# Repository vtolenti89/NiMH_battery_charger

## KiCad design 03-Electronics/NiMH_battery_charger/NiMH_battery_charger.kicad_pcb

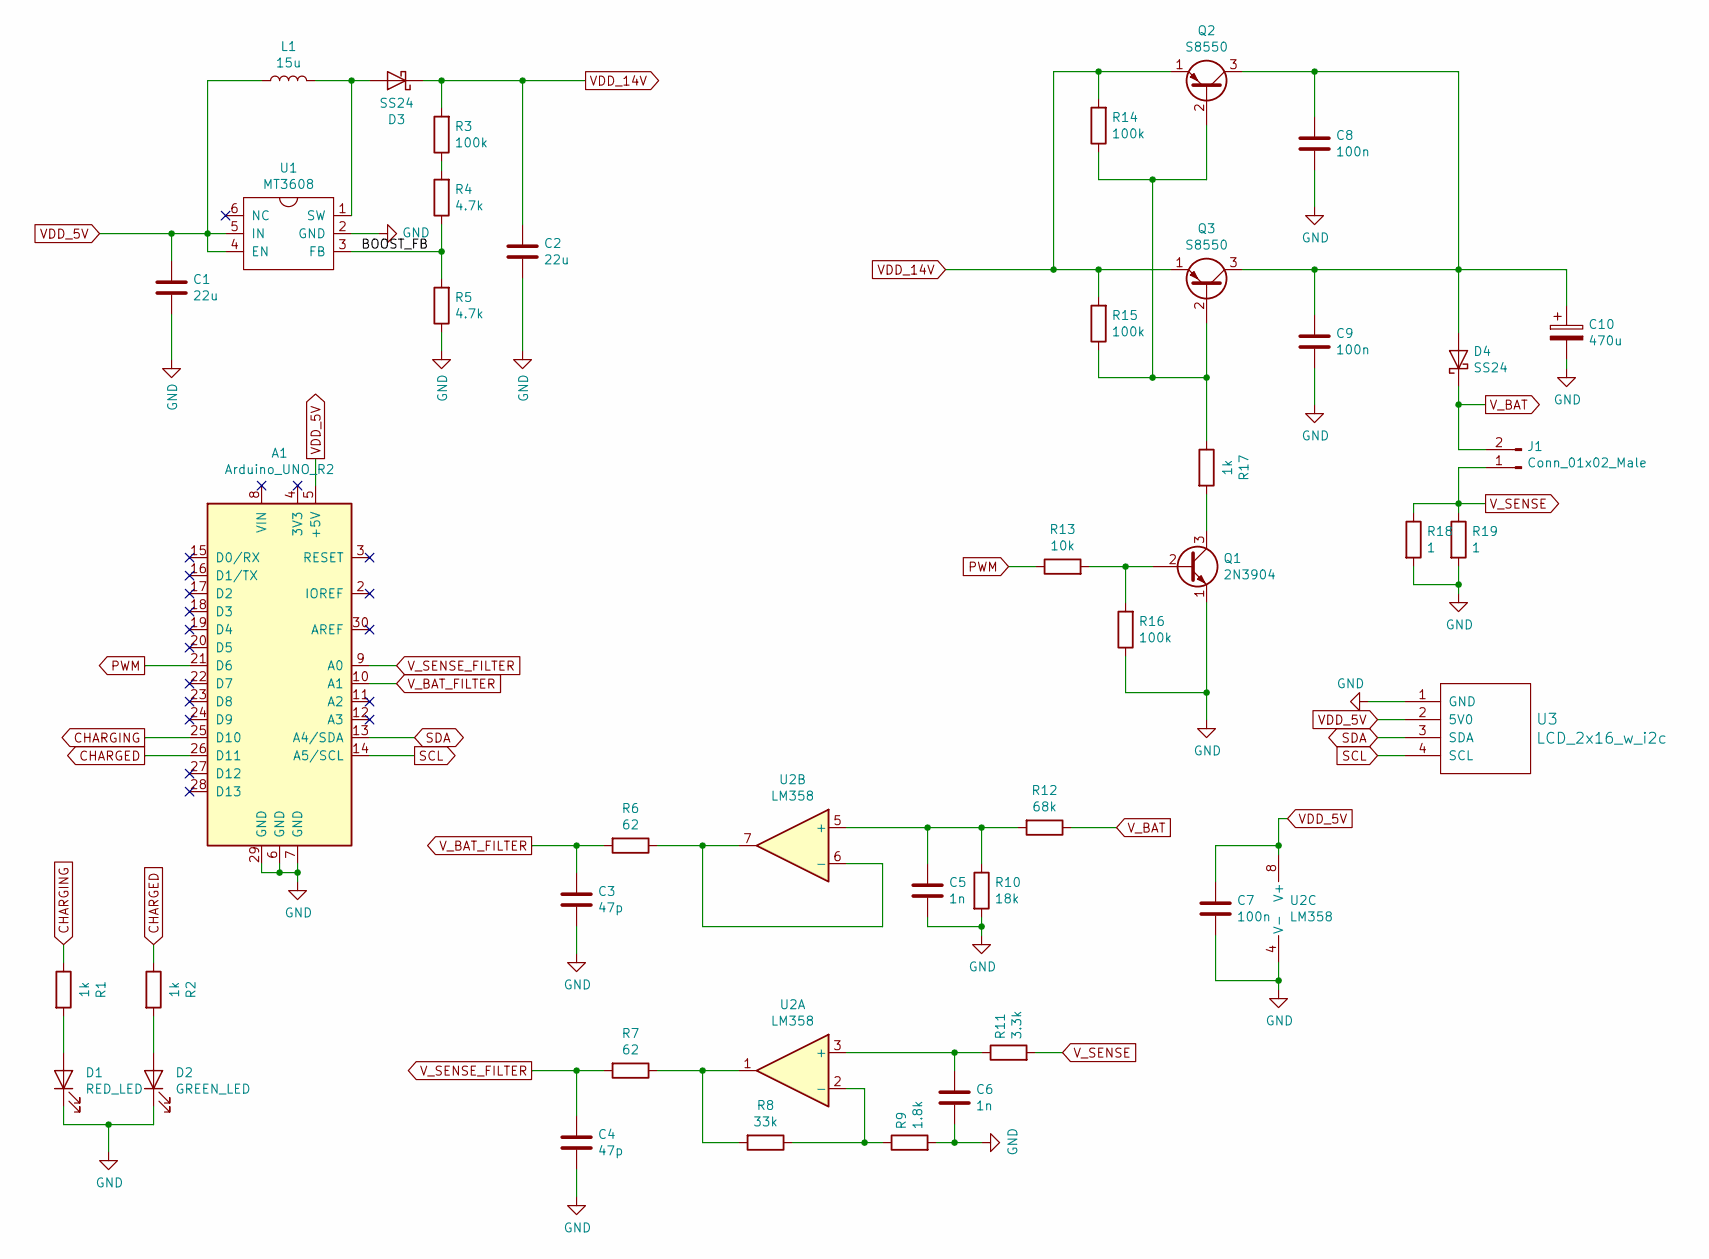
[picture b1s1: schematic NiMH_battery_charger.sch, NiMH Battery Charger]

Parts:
A1: Arduino_UNO_R2
C1, C2: 22u; C_0603_1608Metric_Pad1.05x0.95mm_HandSolder
C3, C4: 47p; C_0603_1608Metric_Pad1.05x0.95mm_HandSolder
C5, C6: 1n; C_0603_1608Metric_Pad1.05x0.95mm_HandSolder
C7, C8, C9: 100n; C_0603_1608Metric_Pad1.05x0.95mm_HandSolder
C10: 470u; CP_Radial_D6.3mm_P2.50mm
D1: RED_LED; LED_1206_3216Metric
D2: GREEN_LED; LED_1206_3216Metric
D3, D4: SS24; SMA_DO-214AC
J1: Conn_01x02_Male; PinSocket_1x02_P2.54mm_Vertical
L1: 15u; CD54
Q1: 2N3904; TO-92_Inline
Q2, Q3: S8550; TO-92_Inline
R1, R2, R17: 1k; R_0603_1608Metric_Pad1.05x0.95mm_HandSolder
R3, R14, R15, R16: 100k; R_0603_1608Metric_Pad1.05x0.95mm_HandSolder
R4, R5: 4.7k; R_0603_1608Metric_Pad1.05x0.95mm_HandSolder
R6, R7: 62; R_0603_1608Metric_Pad1.05x0.95mm_HandSolder
R8: 33k; R_0603_1608Metric_Pad1.05x0.95mm_HandSolder
R9: 1.8k; R_0603_1608Metric_Pad1.05x0.95mm_HandSolder
R10: 18k; R_0603_1608Metric_Pad1.05x0.95mm_HandSolder
R11: 3.3k; R_0603_1608Metric_Pad1.05x0.95mm_HandSolder
R12: 68k; R_0603_1608Metric_Pad1.05x0.95mm_HandSolder
R13: 10k; R_0603_1608Metric_Pad1.05x0.95mm_HandSolder
R18, R19: 1; R_0603_1608Metric_Pad1.05x0.95mm_HandSolder
U1: MT3608; TSOT-23-6
U2: LM358; SOIC-8-1EP_3.9x4.9mm_P1.27mm_EP2.29x3mm
U3: LCD_2x16_w_i2c; PinHeader_1x04_P2.54mm_Vertical

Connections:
/BOOST_FB: R4.1, R5.2, U1.3 (FB)
CHARGED: A1.26 (D11), R2.1
CHARGING: A1.25 (D10), R1.1
GND: A1.6 (GND), A1.7 (GND), A1.29 (GND), C1.2, C2.2, C3.2, C4.2, C5.2, C6.2, C7.2, C8.2, C9.2, C10.2, D1.1 (K), D2.1 (K), Q1.1 (E), R5.1, R9.2, R10.2, R16.1, R18.2, R19.2, U1.2 (GND), U2.4 (V-), U3.1 (GND)
unnamed: C5.1, R10.1, R12.2, U2.5 (+)
unnamed: C6.1, R11.1, U2.3 (+)
unnamed: C8.1, C9.1, C10.1, D4.2 (A), Q2.3 (C), Q3.3 (C)
unnamed: D1.2 (A), R1.2
unnamed: D2.2 (A), R2.2
unnamed: D3.2 (A), L1.2, U1.1 (SW)
unnamed: Q1.2 (B), R13.2, R16.2
unnamed: Q1.3 (C), R17.2
unnamed: Q2.2 (B), Q3.2 (B), R14.1, R15.1, R17.1
unnamed: R3.1, R4.2
unnamed: R6.1, U2.6 (-), U2.7
unnamed: R7.1, R8.2, U2.1
unnamed: R8.1, R9.1, U2.2 (-)
PWM: A1.21 (D6), R13.1
SCL: A1.14 (A5/SCL), U3.4 (SCL)
SDA: A1.13 (A4/SDA), U3.3 (SDA)
VDD_5V: A1.5 (+5V), C1.1, C7.1, L1.1, U1.4 (EN), U1.5 (IN), U2.8 (V+), U3.2 (5V0)
VDD_14V: C2.1, D3.1 (K), Q2.1 (E), Q3.1 (E), R3.2, R14.2, R15.2
V_BAT: D4.1 (K), J1.2, R12.1
V_BAT_FILTER: A1.10 (A1), C3.1, R6.2
V_SENSE: J1.1, R11.2, R18.1, R19.1
V_SENSE_FILTER: A1.9 (A0), C4.1, R7.2

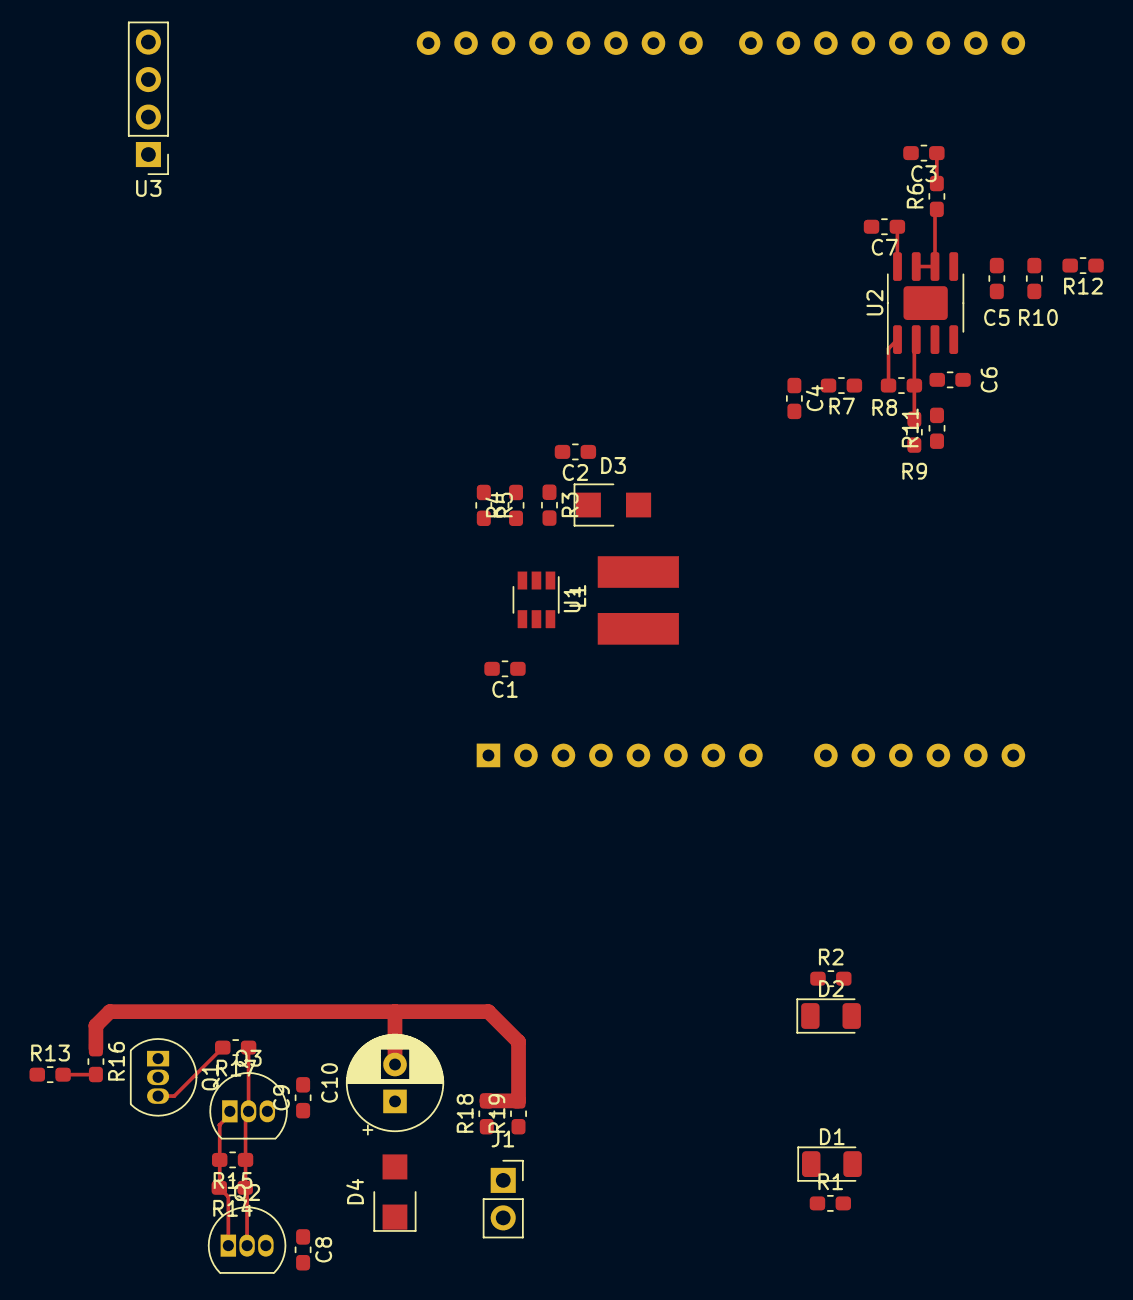
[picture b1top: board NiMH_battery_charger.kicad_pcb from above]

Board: 2 copper layers, 42 parts (1 on the bottom side), 26 nets.

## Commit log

2020-06-04 update schematic
